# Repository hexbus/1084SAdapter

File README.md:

# 1084SAdapter
Universal 1084S Monitor Adapter – DIN ↔ DE9 RGB Adapter/Monitor for Amiga, Tandy, and analog/digital RGB 1980's computers

**Philips DIN ↔ Daewoo DE9 Converter and signal debugger/monitor**

This board adapts between different 1084S monitor standards—commonly found in Philips and Daewoo variants—and allows flexible signal routing for Amiga, CGA-based PCs, and other retro systems.

---

## 🌟 Key Features & Use Cases

This board supports multiple configurations on a 1084S monitor (Magnavox, Philips, etc) from the 1980s and early 1990s:

1. **Philips (DIN-based) to traditional Amiga (DE9)**  
   Use this to connect a DIN-based 1084 monitor (typically Philips) to an Amiga that outputs via DE9 monitor cable.

2. **Daewoo (DE9-based) to traditional Amiga (Analog RGB DIN)**  
   Use this to connect a DE9-based 1084 monitor (typically Daewoo) to an Amiga that outputs via DIN monitor cable.

3. **Cross-compatibility**  
   Adapt any other computer using these connectors to a 15kHz monitor, including hybrid setups.
   (Like a Myarc Geneve 9640 to a 1084S-D1/D2, or a MSX to a 1084S-D1/D2 that had a DIN connection.)

5. **CGA (Tandy 1000) to Philips 1084S (Digital RGB DIN)**  
   Use this board to easily connect DE9 CGA-based PCs to a digital DIN-based monitor like the Philips 1084.  
6. **Real-time signal troubleshooting**  
   Connect two boards back-to-back to test sync and RGB lines without format conversion:  
   ```
   Monitor (Analog RGB input) 
     <-> DIN6 male-male cable 
     <-> Adapter Board 
     <-> DE9 male-male cable 
     <-> Adapter Board 
     <-> DIN6 male (Amiga cable/Amiga)
   ```

7. **Signal analysis and custom monitor adapter testing**  
   Use an oscilloscope with this board while designing new adapters or troubleshooting pinouts by experimenting with sync jumper configurations.  Monitor all sync and RGB lines, and see if you're getting the output you're expecting on all lines.  Helps with troubleshooting no-output situations, and if it's a computer fault, or a monitor fault.

---

## ⚠️ Warning

This board gives you *a lot* of flexibility—but with that comes responsibility.  
Incorrect jumper settings, especially for sync signals, can **damage your monitor**. Be **absolutely certain** you understand what you're doing when adjusting jumper settings (J4–J9). You assume all risk for damage caused by improper usage.

---

## 🔧 Default Configuration

Out of the box, the board routes Horizontal and Vertical Sync directly:

- **J4 (HSYNC)**: Enabled → Position **1–2**  
- **J7 (VSYNC)**: Enabled → Position **1–2**

---

## 🧩 Jumper Reference (Sync Routing)

Use these jumpers to customize how sync signals are routed:

| Jumper | Signal Routed From (DIN) | To (DE9) Pin     | Enabled When | Notes               |
|--------|---------------------------|------------------|--------------|---------------------|
| **J4** | HSYNC                     | HSYNC            | 1–2          | **Default ON**      |
| **J5** | HSYNC                     | VSYNC            | 1–2          | Optional, disabled  |
| **J6** | HSYNC                     | CSYNC            | 1–2          | Optional, disabled  |
| **J7** | VSYNC                     | VSYNC            | 1–2          | **Default ON**      |
| **J8** | VSYNC                     | HSYNC            | 1–2          | Optional, disabled  |
| **J9** | VSYNC                     | CSYNC            | 1–2          | Optional, disabled |

(All jumpers can be stowed in position 2-3 when disabled.)

**Note:** Only enable the jumpers that suit your configuration. Never enable conflicting signals unless you're absolutely sure.

### Example (Hypothetical Scenario):
You have a monitor that **only accepts CSYNC**, but your system provides separate HSYNC and VSYNC via DIN.  
You might try:
- Enable **J9**: VSYNC → CSYNC  
- Optionally enable **J6**: HSYNC → CSYNC  
⚠️ This is theoretical; test carefully and monitor your signals.

---

## 🛒 Bill of Materials (BOM)

| Designator | Part Number / Description                                |
|------------|----------------------------------------------------------|
| **J1**     | TE Connectivity 5211511-1 (DIN-8) or equivalent           |
| **J2**     | TE Connectivity 9-211509-0 (DIN-6) or equivalent          |
| **J3**     | DE9 Female, Right Angle, 2.77×2.84 mm pins, 7.48 mm offset |
| **J4–J9**  | 3-pin standard 2.54 mm headers (6 × 3 = 18 pins total)    |
| **TP1–TP8**| Test points (fit standard 2.54 mm header holes)           |

---

## 📌 Connector Pinouts

These are the relevant pinouts for the **Commodore 1084S** monitor. Understanding these is critical for properly wiring and configuring sync routing via jumpers (J4–J9).

---

### 🔌 J1 – Digital RGB Input (DIN-8, typically Philips models)

| Pin | Name   | Description        |
|-----|--------|--------------------|
| 1   | n/c    | Not connected      |
| 2   | R      | Red                |
| 3   | G      | Green              |
| 4   | B      | Blue               |
| 5   | I      | Intensity          |
| 6   | GND    | Ground             |
| 7   | HSYNC  | Horizontal Sync    |
| 8   | VSYNC  | Vertical Sync      |

---

### 🎨 J2 – Analog RGB Input (DIN-6, typically for Amiga or other analog video sources)

| Pin | Name   | Description        |
|-----|--------|--------------------|
| 1   | G      | Green              |
| 2   | HSYNC  | Horizontal Sync    |
| 3   | GND    | Ground             |
| 4   | R      | Red                |
| 5   | B      | Blue               |
| 6   | VSYNC  | Vertical Sync      |

---

### 🖥️ J3 – DE9 Video Connector (Female, at Monitor)

This connector supports **both analog and digital RGB**, combining signals from the DIN connectors internally.

| Pin | Name   | Analog Mode         | Digital Mode        |
|-----|--------|---------------------|----------------------|
| 1   | GND    | Ground              | Ground               |
| 2   | GND    | Ground              | Ground               |
| 3   | R      | Red                 | Red                  |
| 4   | G      | Green               | Green                |
| 5   | B      | Blue                | Blue                 |
| 6   | I      | *Not Connected*     | Intensity            |
| 7   | CSYNC  | Composite Sync      | *Not Connected*      |
| 8   | HSYNC  | *Not Connected*     | Horizontal Sync      |
| 9   | VSYNC  | *Not Connected*     | Vertical Sync        |

📝 **Note:** The 1084S DE9 connector internally combines analog and digital signals from the two DIN connectors. That’s why this board can act as a bidirectional adapter between Philips-style and Daewoo-style 1084S monitors.

---

## 📷 Diagrams & Visuals

Pinout diagrams (DIN-6, DIN-8, and DE9) coming soon!

---

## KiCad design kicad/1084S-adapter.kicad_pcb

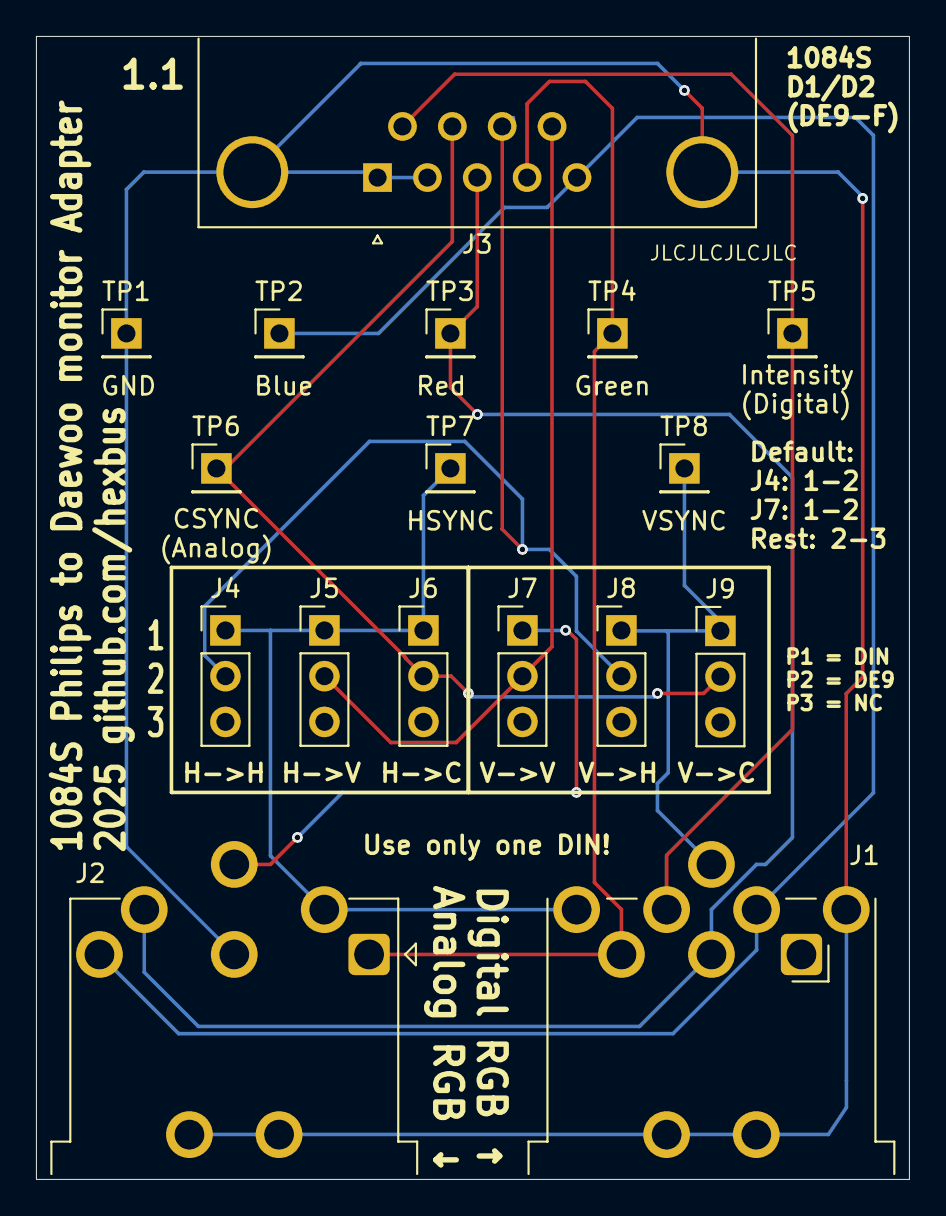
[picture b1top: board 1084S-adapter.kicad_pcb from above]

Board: 2 copper layers, 48.5 x 63.5 mm, 17 parts (0 on the bottom side), 10 nets.

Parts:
J1: TE_5211511-1_DIN-8_Circular
J2: TE_9-211509-0_DIN-6_Circular
J3: Connector_Dsub:DSUB-9_Female_Horizontal_P2.77x2.8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; DSUB-9_Female_Horizontal_P2.77x2.84mm_EdgePinOffset4.94mm_H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
J4: H->H; PinHeader_1x03_P2.54mm_Vertical
J5: H->V; PinHeader_1x03_P2.54mm_Vertical
J6: H->C; PinHeader_1x03_P2.54mm_Vertical
J7: V->V; PinHeader_1x03_P2.54mm_Vertical
J8: V->H; PinHeader_1x03_P2.54mm_Vertical
J9: V->C; PinHeader_1x03_P2.54mm_Vertical
TP1: P1+2 GND; PinHeader_1x01_P2.54mm_Vertical
TP2: Pin 5 Blue; PinHeader_1x01_P2.54mm_Vertical
TP3: Pin 3 RED; PinHeader_1x01_P2.54mm_Vertical
TP4: Pin 4 GREEN; PinHeader_1x01_P2.54mm_Vertical
TP5: P6 Intensity (Dig); PinHeader_1x01_P2.54mm_Vertical
TP6: Pin 7 CSYNC (Ana); PinHeader_1x01_P2.54mm_Vertical
TP7: Pin 8 HSYNC; PinHeader_1x01_P2.54mm_Vertical
TP8: Pin 9 VSYNC; PinHeader_1x01_P2.54mm_Vertical

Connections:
/BLUE: J1.4, J2.5, J3.5, TP2.1
/CSYNC9: J3.7, J6.2, J9.2, TP6.1
/GND: J1.0, J1.6, J2.0, J2.3, J3.0 (PAD), J3.1, J3.2, TP1.1
/GREEN: J1.3, J2.1, J3.4, TP4.1
/HSYNC: J1.7, J2.2, J4.1, J5.1, J6.1, TP7.1
/INTENSITY: J1.5, J3.6, TP5.1
/RED: J1.2, J2.4, J3.3, TP3.1
/VSYNC: J1.8, J2.6, J7.1, J8.1, J9.1, TP8.1
HSYNC9: J3.8, J4.2, J8.2
VSYNC9: J3.9, J5.2, J7.2
